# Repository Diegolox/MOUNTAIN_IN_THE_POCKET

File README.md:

# MOUNTAIN IN THE POCKET ⛰️
Un dispositivo que va  ayudar a muchos montañeros en sus expediciones.

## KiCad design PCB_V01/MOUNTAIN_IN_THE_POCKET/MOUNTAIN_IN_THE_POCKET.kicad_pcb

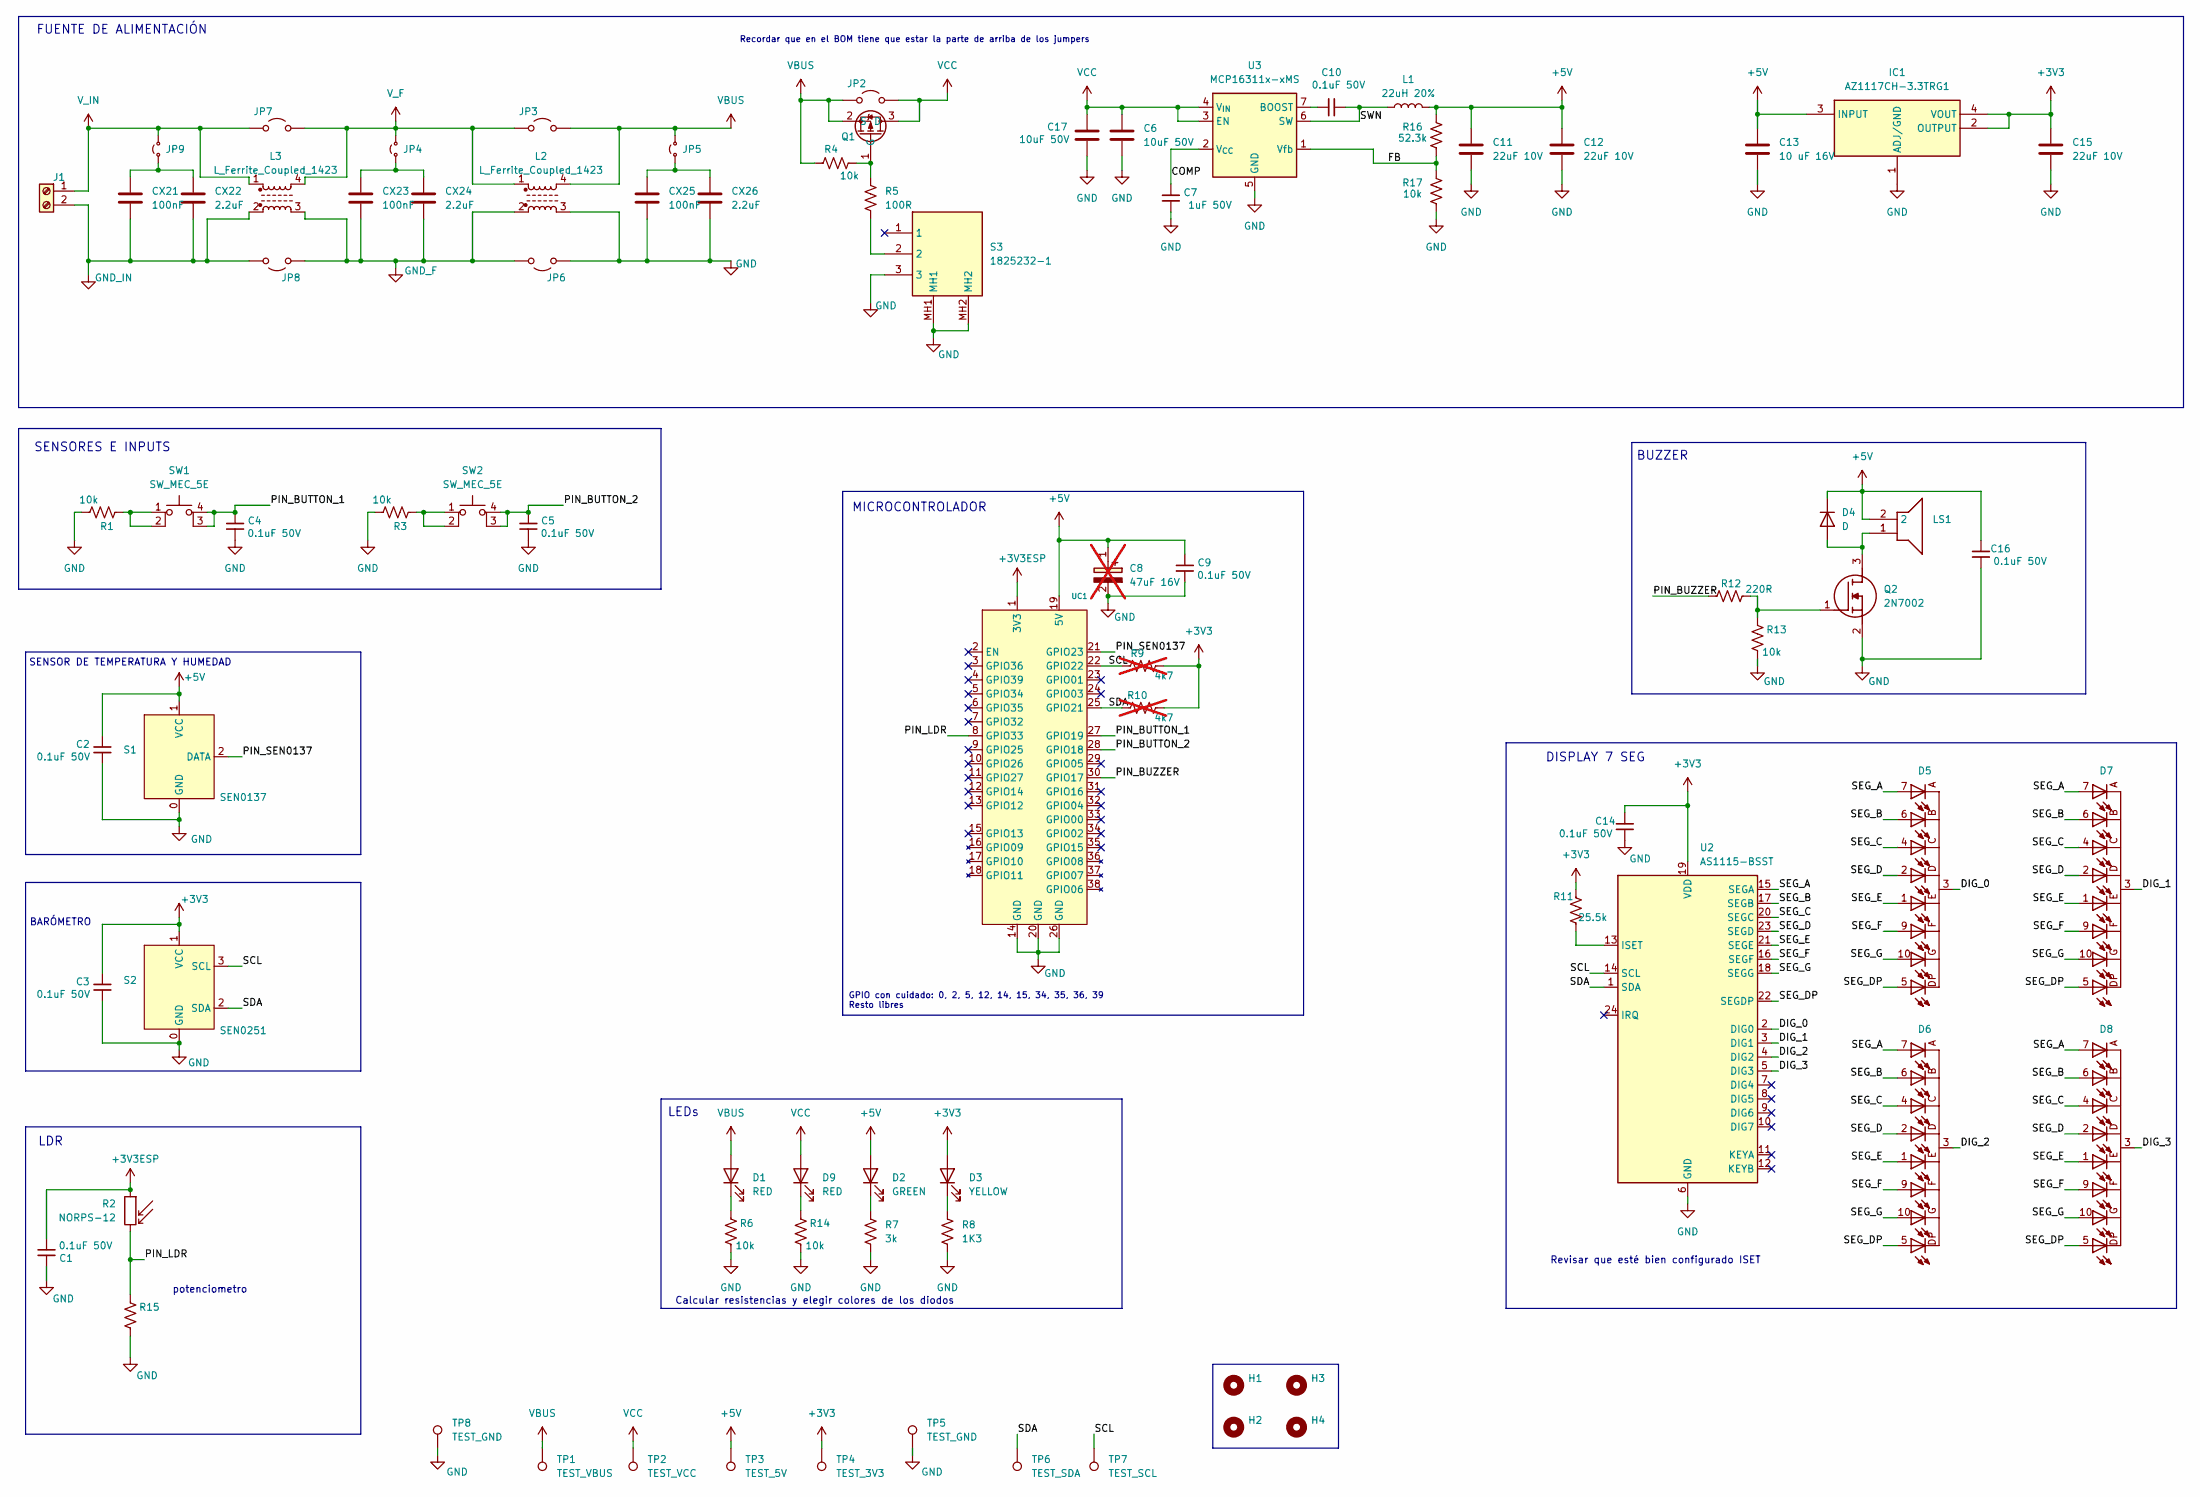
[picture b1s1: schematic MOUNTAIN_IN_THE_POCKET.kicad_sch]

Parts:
C1, C2, C3, C4, C5, C9, C10, C14, C16: 0.1uF 50V; C_0805_2012Metric_Pad1.18x1.45mm_HandSolder
C6, C17: 10uF 50V; C_1206_3216Metric_Pad1.33x1.80mm_HandSolder
C7: 1uF 50V; C_0805_2012Metric_Pad1.18x1.45mm_HandSolder
C8: 47uF 16V; CAPAE660X570N; Manufacturer_Part_Number 865230343004; not fitted
C11, C12, C15: 22uF 10V; C_1206_3216Metric_Pad1.33x1.80mm_HandSolder
C13: 10 uF 16V; C_1206_3216Metric_Pad1.33x1.80mm_HandSolder
CX21, CX23, CX25: 100nF; C_0805_2012Metric_Pad1.18x1.45mm_HandSolder
CX22, CX24, CX26: 2.2uF; C_1206_3216Metric_Pad1.33x1.80mm_HandSolder
D1, D9: RED; LED_1206_3216Metric_Pad1.42x1.75mm_HandSolder
D2: GREEN; LED_1206_3216Metric_Pad1.42x1.75mm_HandSolder
D3: YELLOW; LED_1206_3216Metric_Pad1.42x1.75mm_HandSolder
D4: D; D_SMA_Handsoldering
D5, D6, D7, D8: 14.2mm_157142S12703; D_Wurth_WL-T7DS-14.2mm; Part Number 157142S12703
H1, H2, H3, H4: MountingHole; MountingHole_3.2mm_M3
IC1: AZ1117CH-3.3TRG1; SOT230P700X180-4N; Manufacturer_Part_Number AZ1117CH-3.3TRG1
J1: CON_ALIM; TerminalBlock_Phoenix_MKDS-1,5-2-5.08_1x02_P5.08mm_Horizont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
JP2, JP3, JP6, JP7, JP8: Jumper_2_Open; PinHeader_2x01_P2.54mm_Vertical
JP4, JP5, JP9: Jumper_2_Small_Open; PinHeader_2x01_P2.54mm_Vertical
L1: 22uH 20%; IFSC2020DEER4R7M01
L2: L_Ferrite_Coupled_1423; DIPS508W60P254L640H800Q4N
L3: L_Ferrite_Coupled_1423; SU9VF05030
LS1: MCKPX-G1205A-3700; CEM1205IC; Manufacturer_Part_Number MCKPX-G1205A-3700; Farnell Part Number 2135914
Q1: TSOT-23_HandSoldering
Q2: 2N7002; SOT-23_Handsoldering; Manufacturer_Part_Number 2N7002
R1, R3, R4, R6, R13: 10k; R_1206_3216Metric_Pad1.30x1.75mm_HandSolder
R2: NORPS-12; R_LDR_5.1x4.3mm_P3.4mm_Vertical
R5: 100R; R_1206_3216Metric_Pad1.30x1.75mm_HandSolder
R7: 3k; R_1206_3216Metric_Pad1.30x1.75mm_HandSolder
R8: 1K3; R_1206_3216Metric_Pad1.30x1.75mm_HandSolder
R9, R10: 4k7; R_1206_3216Metric_Pad1.30x1.75mm_HandSolder; not fitted
R11: 25.5k; R_1206_3216Metric_Pad1.30x1.75mm_HandSolder
R12: 220R; R_1206_3216Metric_Pad1.30x1.75mm_HandSolder
R14, R17: 10k; R_0805_2012Metric_Pad1.20x1.40mm_HandSolder
R15: R_1206_3216Metric_Pad1.30x1.75mm_HandSolder
R16: 52.3k; R_0805_2012Metric_Pad1.20x1.40mm_HandSolder
S1: SEN0137; CONECTOR_0137
S2: SEN0251; CONECTOR_0251
S3: 1825232-1; 18252321; Manufacturer_Part_Number 1825232-1
SW1, SW2: SW_MEC_5E; TL3305AF160QG
TP1: TEST_VBUS; TestPoint_THTPad_D1.0mm_Drill0.5mm
TP2: TEST_VCC; TestPoint_THTPad_D1.0mm_Drill0.5mm
TP3: TEST_5V; TestPoint_THTPad_D1.0mm_Drill0.5mm
TP4: TEST_3V3; TestPoint_THTPad_D1.0mm_Drill0.5mm
TP5, TP8: TEST_GND; TestPoint_THTPad_D1.0mm_Drill0.5mm
TP6: TEST_SDA; TestPoint_THTPad_D1.0mm_Drill0.5mm
TP7: TEST_SCL; TestPoint_THTPad_D1.0mm_Drill0.5mm
U2: AS1115-BSST; QSOP-24_3.9x8.7mm_P0.635mm
U3: MCP16311x-xMS; MSOP-8_3x3mm_P0.65mm
UC1: ESP32_WROOM32_SHIELD_V01

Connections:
+3V3: C3.1, C14.1, C15.1, D3.2 (A), IC1.2 (OUTPUT), IC1.4 (VOUT), R9.2, R10.2, R11.1, S2.1 (VCC), TP4.1 (1_1), U2.19 (VDD)
+3V3ESP: C1.2, R2.1, UC1.1 (3V3)
+5V: C2.1, C8.1 (+), C9.1, C11.1, C12.1, C13.1, C16.1, D2.2 (A), D4.1 (K), IC1.3 (INPUT), L1.2, LS1.2 (2_2), R16.1, S1.1 (VCC), TP3.1 (1_1), UC1.19 (5V)
/COMP: C7.1, U3.2 (V_{CC})
/DIG_0: D5.3, D5.8, U2.2 (DIG0)
/DIG_1: D7.3, D7.8, U2.3 (DIG1)
/DIG_2: D6.3, D6.8, U2.4 (DIG2)
/DIG_3: D8.3, D8.8, U2.5 (DIG3)
/FB: R16.2, R17.1, U3.1 (Vfb)
/PIN_BUTTON_1: C4.1, SW1.3 (K), SW1.4 (A), UC1.27 (GPIO19)
/PIN_BUTTON_2: C5.1, SW2.3 (K), SW2.4 (A), UC1.28 (GPIO18)
/PIN_BUZZER: R12.2, UC1.30 (GPIO17)
/PIN_LDR: R2.2, R15.2, UC1.8 (GPIO33)
/PIN_SEN0137: S1.2 (DATA), UC1.21 (GPIO23)
/SCL: R9.1, S2.3 (SCL), TP7.1 (1_1), U2.14 (SCL), UC1.22 (GPIO22)
/SDA: R10.1, S2.2 (SDA), TP6.1 (1_1), U2.1 (SDA), UC1.25 (GPIO21)
/SEG_A: D5.7 (A), D6.7 (A), D7.7 (A), D8.7 (A), U2.15 (SEGA)
/SEG_B: D5.6 (B), D6.6 (B), D7.6 (B), D8.6 (B), U2.17 (SEGB)
/SEG_C: D5.4 (C), D6.4 (C), D7.4 (C), D8.4 (C), U2.20 (SEGC)
/SEG_D: D5.2 (D), D6.2 (D), D7.2 (D), D8.2 (D), U2.23 (SEGD)
/SEG_DP: D5.5 (DP), D6.5 (DP), D7.5 (DP), D8.5 (DP), U2.22 (SEGDP)
/SEG_E: D5.1 (E), D6.1 (E), D7.1 (E), D8.1 (E), U2.21 (SEGE)
/SEG_F: D5.9 (F), D6.9 (F), D7.9 (F), D8.9 (F), U2.16 (SEGF)
/SEG_G: D5.10 (G), D6.10 (G), D7.10 (G), D8.10 (G), U2.18 (SEGG)
/SWN: C10.2, L1.1, U3.6 (SW)
GND: C1.1, C2.2, C3.2, C4.2, C5.2, C6.2, C7.2, C8.2 (-), C9.2, C11.2, C12.2, C13.2, C14.2, C15.2, C16.2, C17.2, CX25.2, CX26.2, IC1.1 (ADJ/GND), JP6.1 (A), L2.3, Q2.2 (S), R1.1, R3.1, R6.1, R7.1, R8.1, R13.1, R14.1, R15.1, R17.2, S1.0 (GND), S2.0 (GND), S3.3, S3.MH1, S3.MH2, TP5.1 (1_1), TP8.1 (1_1), U2.6 (GND), U3.5 (GND), U3.8 (GND), UC1.14 (GND), UC1.20 (GND), UC1.26 (GND)
GND_F: CX23.2, CX24.2, JP6.2 (B), JP8.1 (A), L2.2, L3.3
GND_IN: CX21.2, CX22.2, J1.2, JP8.2 (B), L3.2
unnamed: D1.1 (K), R6.2
unnamed: D2.1 (K), R7.2
unnamed: D3.1 (K), R8.2
unnamed: D4.2 (A), LS1.1, Q2.3 (D)
unnamed: D9.1 (K), R14.2
unnamed: CX23.1, CX24.1, JP4.1 (A)
unnamed: CX25.1, CX26.1, JP5.1 (A)
unnamed: CX21.1, CX22.1, JP9.1 (A)
unnamed: Q1.1 (G), R4.1, R5.1
unnamed: Q2.1 (G), R12.1, R13.2
unnamed: R1.2, SW1.1, SW1.2
unnamed: R3.2, SW2.1, SW2.2
unnamed: R5.2, S3.2
unnamed: R11.2, U2.13 (ISET)
unnamed: C10.1, U3.7 (BOOST)
VBUS: D1.2 (A), JP2.1 (A), JP3.2 (B), JP5.2 (B), L2.4, Q1.2 (S), R4.2, TP1.1 (1_1)
VCC: C6.1, C17.1, D9.2 (A), JP2.2 (B), Q1.3 (D), TP2.1 (1_1), U3.3 (EN), U3.4 (V_{IN})
V_F: JP3.1 (A), JP4.2 (B), JP7.2 (B), L2.1, L3.4
V_IN: J1.1, JP7.1 (A), JP9.2 (B), L3.1

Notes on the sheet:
DISPLAY 7 SEG
FUENTE DE ALIMENTACIÓN
BARÓMETRO
SENSORES E INPUTS
Recordar que en el BOM tiene que estar la parte de arriba de los jumpers
SENSOR DE TEMPERATURA Y HUMEDAD
GPIO con cuidado: 0, 2, 5, 12, 14, 15, 34, 35, 36, 39 Resto libres
BUZZER
MICROCONTROLADOR
Calcular resistencias y elegir colores de los diodos
LDR
potenciometro
Revisar que esté bien configurado ISET
LEDs

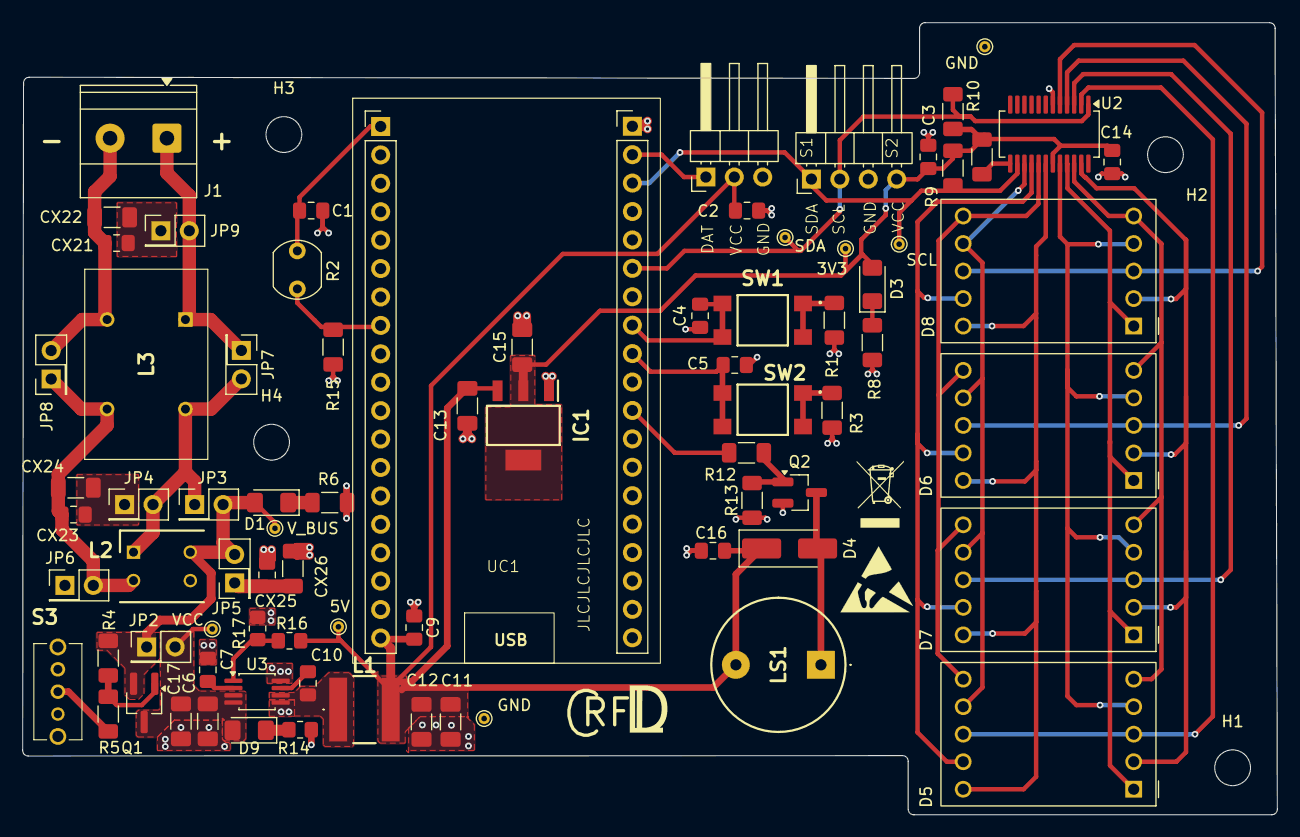
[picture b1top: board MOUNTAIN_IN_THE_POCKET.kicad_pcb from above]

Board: 2 copper layers, 112.1 x 70.8 mm, 82 parts (0 on the bottom side), 46 nets.

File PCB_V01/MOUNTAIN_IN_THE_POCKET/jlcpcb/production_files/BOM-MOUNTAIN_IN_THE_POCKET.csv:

Comment,Designator,Footprint,LCSC,Quantity
10k,R13,R_1206_3216Metric_Pad1.30x1.75mm_HandSolder,,1
22uF 10V,C12,C_1206_3216Metric_Pad1.33x1.80mm_HandSolder,,1
Jumper_2_Small_Open,JP4,PinHeader_2x01_P2.54mm_Vertical,,1
2.2uF,CX26,C_1206_3216Metric_Pad1.33x1.80mm_HandSolder,,1
~,R15,R_1206_3216Metric_Pad1.30x1.75mm_HandSolder,,1
10k,R14,R_0805_2012Metric_Pad1.20x1.40mm_HandSolder,,1
SW_MEC_5E,SW1,TL3305AF160QG,,1
SEN0137,S1,CONECTOR_0137,,1
14.2mm_157142S12703,D7,D_Wurth_WL-T7DS-14.2mm,,1
SEN0251,S2,CONECTOR_0251,,1
D,D4,D_SMA_Handsoldering,,1
1825232-1,S3,18252321,,1
0.1uF 50V,C10,C_0805_2012Metric_Pad1.18x1.45mm_HandSolder,,1
0.1uF 50V,C16,C_0805_2012Metric_Pad1.18x1.45mm_HandSolder,,1
10k,R3,R_1206_3216Metric_Pad1.30x1.75mm_HandSolder,,1
10 uF 16V,C13,C_1206_3216Metric_Pad1.33x1.80mm_HandSolder,,1
14.2mm_157142S12703,D8,D_Wurth_WL-T7DS-14.2mm,,1
100nF,CX23,C_0805_2012Metric_Pad1.18x1.45mm_HandSolder,,1
1K3,R8,R_1206_3216Metric_Pad1.30x1.75mm_HandSolder,,1
27k,R11,R_1206_3216Metric_Pad1.30x1.75mm_HandSolder,,1
L_Ferrite_Coupled_1423,L3,SU9VF05030,,1
~,Q1,TSOT-23_HandSoldering,,1
14.2mm_157142S12703,D5,D_Wurth_WL-T7DS-14.2mm,,1
0.1uF 50V,C2,C_0805_2012Metric_Pad1.18x1.45mm_HandSolder,,1
RED,D1,LED_1206_3216Metric_Pad1.42x1.75mm_HandSolder,,1
0.1uF 50V,C1,C_0805_2012Metric_Pad1.18x1.45mm_HandSolder,,1
2N7002,Q2,SOT-23_Handsoldering,,1
SW_MEC_5E,SW2,TL3305AF160QG,,1
10k,R17,R_0805_2012Metric_Pad1.20x1.40mm_HandSolder,,1
AZ1117CH-3.3TRG1,IC1,SOT230P700X180-4N,,1
22uF 10V,C15,C_1206_3216Metric_Pad1.33x1.80mm_HandSolder,,1
Jumper_2_Small_Open,JP9,PinHeader_2x01_P2.54mm_Vertical,,1
0.1uF 50V,C5,C_0805_2012Metric_Pad1.18x1.45mm_HandSolder,,1
100R,R5,R_1206_3216Metric_Pad1.30x1.75mm_HandSolder,,1
0.1uF 50V,C14,C_0805_2012Metric_Pad1.18x1.45mm_HandSolder,,1
L_Ferrite_Coupled_1423,L2,DIPS508W60P254L640H800Q4N,,1
22uF 10V,C11,C_1206_3216Metric_Pad1.33x1.80mm_HandSolder,,1
Jumper_2_Small_Open,JP5,PinHeader_2x01_P2.54mm_Vertical,,1
RED,D9,LED_1206_3216Metric_Pad1.42x1.75mm_HandSolder,,1
MCP16311x-xMS,U3,MSOP-8_3x3mm_P0.65mm,,1
4k7,,R_1206_3216Metric_Pad1.30x1.75mm_HandSolder,,0
2.2uF,CX24,C_1206_3216Metric_Pad1.33x1.80mm_HandSolder,,1
10uF 50V,C17,C_1206_3216Metric_Pad1.33x1.80mm_HandSolder,,1
100nF,CX25,C_0805_2012Metric_Pad1.18x1.45mm_HandSolder,,1
Jumper_2_Open,JP2,PinHeader_2x01_P2.54mm_Vertical,,1
14.2mm_157142S12703,D6,D_Wurth_WL-T7DS-14.2mm,,1
2.2uF,CX22,C_1206_3216Metric_Pad1.33x1.80mm_HandSolder,,1
10k,R4,R_1206_3216Metric_Pad1.30x1.75mm_HandSolder,,1
100nF,CX21,C_0805_2012Metric_Pad1.18x1.45mm_HandSolder,,1
10k,R1,R_1206_3216Metric_Pad1.30x1.75mm_HandSolder,,1
0.1uF 50V,C3,C_0805_2012Metric_Pad1.18x1.45mm_HandSolder,,1
YELLOW,D3,LED_1206_3216Metric_Pad1.42x1.75mm_HandSolder,,1
CEM-1205-IC,LS1,CEM1205IC,,1
0.1uF 50V,C9,C_0805_2012Metric_Pad1.18x1.45mm_HandSolder,,1
22uH 20%,L1,IFSC2020DEER4R7M01,,1
220R,R12,R_1206_3216Metric_Pad1.30x1.75mm_HandSolder,,1
10uF 50V,C6,C_1206_3216Metric_Pad1.33x1.80mm_HandSolder,,1
AS1115-BSST,U2,QSOP-24_3.9x8.7mm_P0.635mm,,1
10k,R6,R_1206_3216Metric_Pad1.30x1.75mm_HandSolder,,1
0.1uF 50V,C4,C_0805_2012Metric_Pad1.18x1.45mm_HandSolder,,1
52.3k,R16,R_0805_2012Metric_Pad1.20x1.40mm_HandSolder,,1
4k7,,R_1206_3216Metric_Pad1.30x1.75mm_HandSolder,,0
1uF 50V,C7,C_0805_2012Metric_Pad1.18x1.45mm_HandSolder,,1
